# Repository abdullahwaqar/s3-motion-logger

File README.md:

# S3 Motion Logger

ESP32-S3 motion logging board. It logs 6-axis IMU data to a microSD card and streams it over USB, BLE or Wi-Fi. It runs from a single-cell LiPo and charges over USB-C.

**Schematic:** [docs/s3-motion-logger-schematic.pdf](docs/s3-motion-logger-schematic.pdf)

## Specs

|            |                                                        |
| ---------- | ------------------------------------------------------ |
| MCU        | ESP32-S3-WROOM-1-N16R8 (16 MB flash, 8 MB octal PSRAM) |
| IMU        | ICM-42688-P, 4-wire SPI, data-ready interrupt          |
| Storage    | microSD, SDMMC 4-bit                                   |
| Power in   | USB-C, 5 V                                             |
| Battery    | 1S LiPo, JST-PH, charged at 500 mA                     |
| Charger    | BQ24074 with power path (board runs while charging)    |
| 3.3 V rail | TPS63802 buck-boost, 600 mA design budget              |
| Expansion  | Qwiic (I2C) with cuttable pull-ups                     |
| Board      | 50 x 44.5 mm, 4 layers, 1.6 mm, JLCPCB-oriented rules  |

## Block diagram

## Design decisions

- **Charger boots in a safe mode.** The BQ24074 defaults to 500 mA through the EN1/EN2 pull resistors. Firmware raises the input limit only after reading the USB-C CC voltage on the ADC and confirming a 1.5 A or 3 A source.
- **Buck-boost instead of an LDO.** The TPS63802 holds 3.3 V while the battery sags below 3.3 V. Output is set by a 511k/91k divider to 3.31 V.
- **Reverse battery protection.** A P-FET in the battery line protects the charger. JST LiPo polarity is not standardized between vendors, so this is a common failure on real boards.
- **Switched battery sense.** A divider gated by a P-FET and an N-FET draws no current when idle. It reads on ADC1.
- **USB-C done properly.** Separate 5.1k Rd on CC1 and CC2, ESD protection (USBLC6-2SC6) at the connector, and D+/D- defined as a differential pair.
- **GPIO map avoids known traps.** No use of the strapping pins, the octal PSRAM pins (IO35 to IO37), or ADC2 (unusable while Wi-Fi is running). Full map on the MCU sheet.
- **Datasheet-driven parts.** Pinouts and decoupling for the TPS63802 and ICM-42688-P were taken from the TI and TDK datasheets, with custom symbols in `motion_logger.kicad_sym`.
- **Stackup.** L1 signal and parts, L2 solid GND, L3 3V3, L4 signal and GND fill. The antenna sits at the board edge with a copper keep-out on all layers.

## Layout

## Power budget (3.3 V rail)

| Load                | Typical              | Peak             |
| ------------------- | -------------------- | ---------------- |
| ESP32-S3 (Wi-Fi TX) | 30 to 80 mA with BLE | about 350 mA     |
| microSD writes      | 20 mA                | about 100 mA     |
| ICM-42688-P         | about 1 mA           | about 1 mA       |
| LEDs, pull-ups      | about 5 mA           | about 5 mA       |
| **Total**           | **60 to 110 mA**     | **about 460 mA** |

## Open items

1. **No firmware yet.**

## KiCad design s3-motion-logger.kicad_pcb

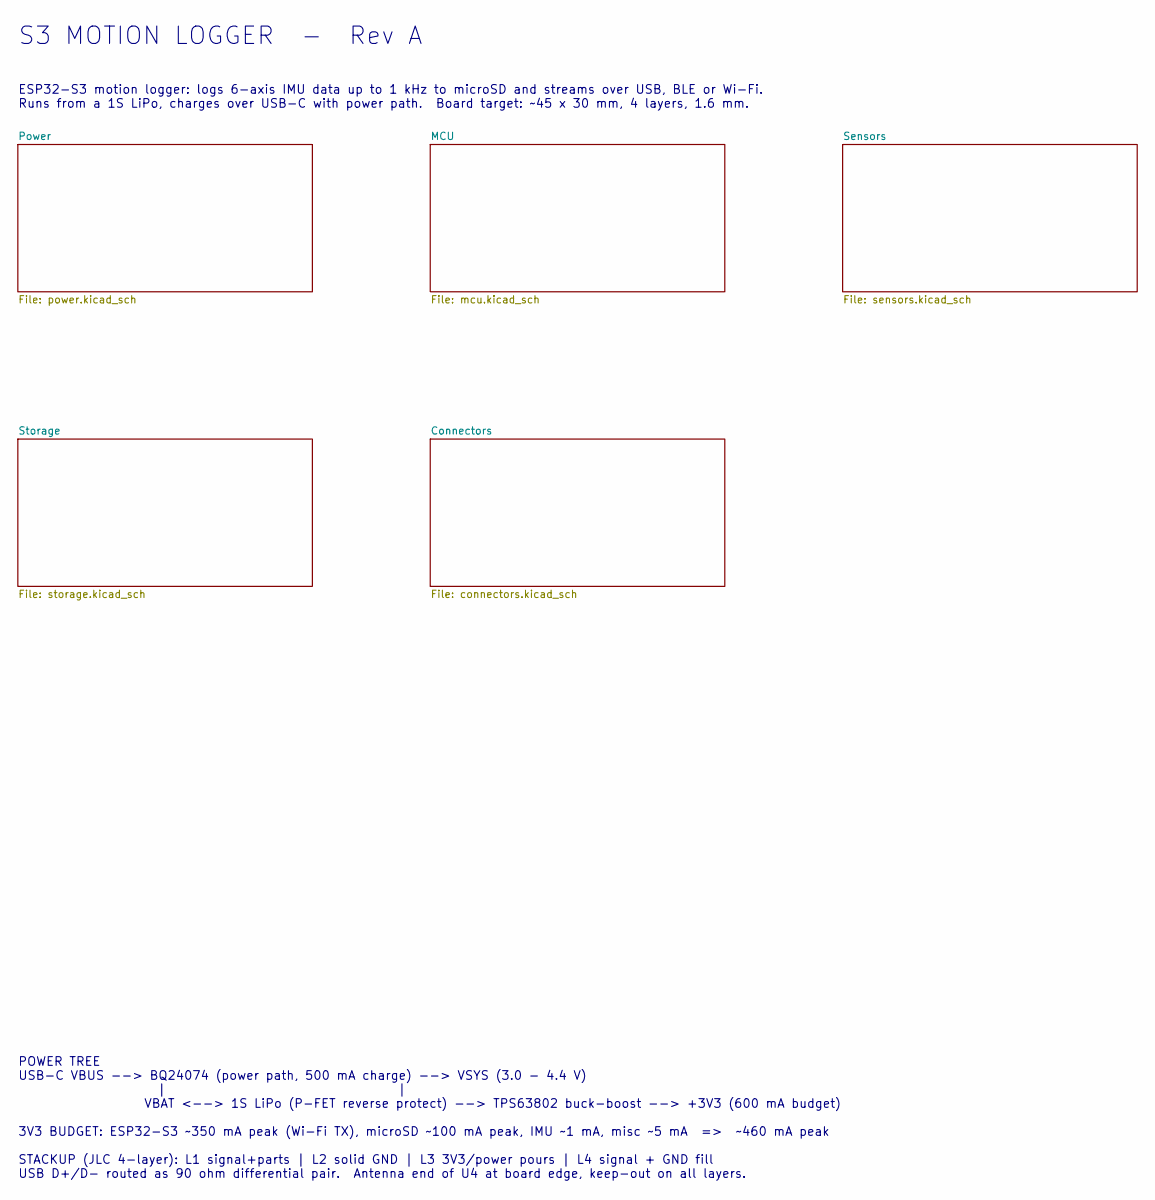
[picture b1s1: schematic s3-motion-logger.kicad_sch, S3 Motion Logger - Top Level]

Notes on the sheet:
S3 MOTION LOGGER - Rev A
ESP32-S3 motion logger: logs 6-axis IMU data up to 1 kHz to microSD and streams over USB, BLE or Wi-Fi. Runs from a 1S LiPo, charges over USB-C with power path. Board target: ~45 x 30 mm, 4 layers, 1.6 mm.
POWER TREE USB-C VBUS --> BQ24074 (power path, 500 mA charge) --> VSYS (3.0 - 4.4 V) | | VBAT <--> 1S LiPo (P-FET reverse protect) --> TPS63802 buck-boost --> +3V3 (600 mA budget) 3V3 BUDGET: ESP32-S3 ~350 mA peak (Wi-Fi TX), microSD ~100 mA peak, IMU ~1 mA, misc ~5 mA => ~460 mA peak STACKUP (JLC 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

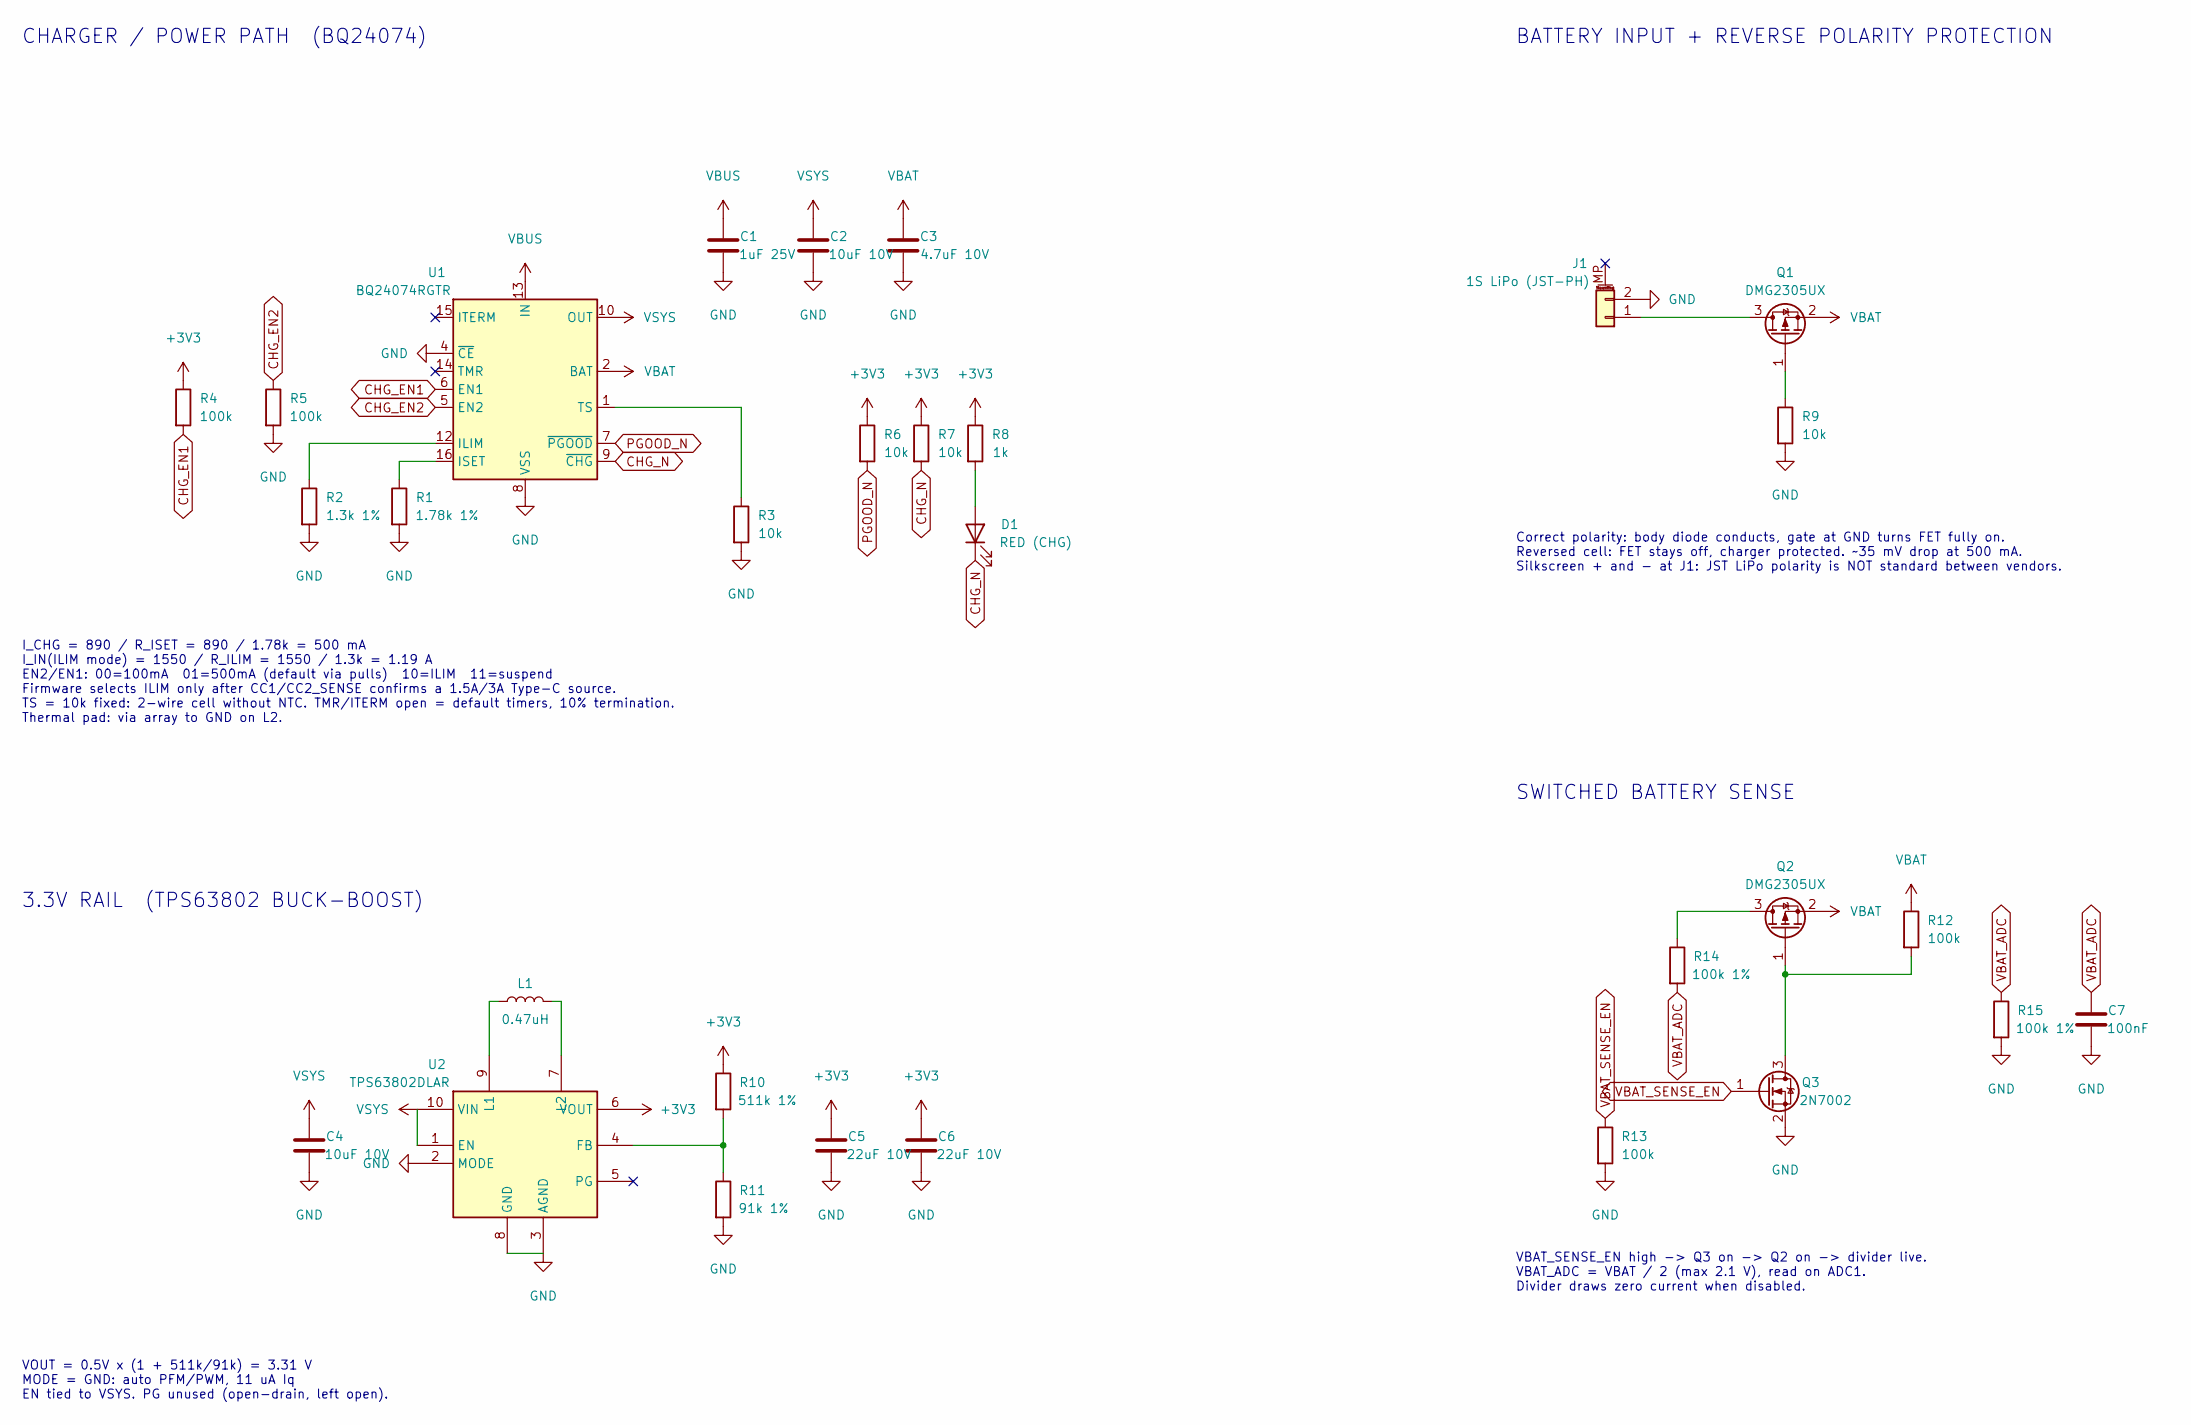
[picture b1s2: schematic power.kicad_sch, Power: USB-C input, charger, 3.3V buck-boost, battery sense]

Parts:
C1: 1uF 25V; C_0603_1608Metric
C2, C4: 10uF 10V; C_0603_1608Metric
C3: 4.7uF 10V; C_0603_1608Metric
C5, C6: 22uF 10V; C_0603_1608Metric
C7: 100nF; C_0402_1005Metric
D1: RED (CHG); LED_0603_1608Metric
J1: 1S LiPo (JST-PH); JST_PH_S2B-PH-SM4-TB_1x02-1MP_P2.00mm_Horizontal; MPN S2B-PH-SM4-TB
L1: 0.47uH; L_Murata_DFE201610P; MPN DFE201610E-R47M=P2
Q1, Q2: DMG2305UX; SOT-23; MPN DMG2305UX-7
Q3: 2N7002; SOT-23; MPN 2N7002
R1: 1.78k 1%; R_0402_1005Metric
R2: 1.3k 1%; R_0402_1005Metric
R3, R6, R7, R9: 10k; R_0402_1005Metric
R4, R5, R12, R13: 100k; R_0402_1005Metric
R8: 1k; R_0402_1005Metric
R10: 511k 1%; R_0402_1005Metric
R11: 91k 1%; R_0402_1005Metric
R14, R15: 100k 1%; R_0402_1005Metric
U1: BQ24074RGTR; VQFN-16-1EP_3x3mm_P0.5mm_EP1.6x1.6mm_ThermalVias; MPN BQ24074RGTR
U2: TPS63802DLAR; TPS63802_DLA_PLACEHOLDER; MPN TPS63802DLAR

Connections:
+3V3: C5.1, C6.1, R4.1, R6.1, R7.1, R8.1, R10.1, U2.6 (VOUT); also elsewhere on the board
BATT_IN: J1.1, Q1.3 (D)
CHGLED_A: D1.2 (A), R8.2
CHG_EN1: R4.2, U1.6 (EN1); also elsewhere on the board
CHG_EN2: R5.1, U1.5 (EN2); also elsewhere on the board
CHG_N: D1.1 (K), R7.2, U1.9 (~CHG); also elsewhere on the board
FB: R10.2, R11.1, U2.4 (FB)
GND: C1.2, C2.2, C3.2, C4.2, C5.2, C6.2, C7.2, J1.2, Q3.2 (S), R1.2, R2.2, R3.2, R5.2, R9.2, R11.2, R13.2, R15.2, U1.4 (~CE), U1.8 (VSS), U1.17 (VSS), U2.2 (MODE), U2.3 (AGND), U2.8 (GND); also elsewhere on the board
ILIM: R2.1, U1.12 (ILIM)
ISET: R1.1, U1.16 (ISET)
PGOOD_N: R6.2, U1.7 (~PGOOD); also elsewhere on the board
Q1_G: Q1.1 (G), R9.1
Q2_G: Q2.1 (G), Q3.3 (D), R12.2
SW1: L1.1, U2.9 (L1)
SW2: L1.2, U2.7 (L2)
TS: R3.1, U1.1 (TS)
VBAT: C3.1, Q1.2 (S), Q2.2 (S), R12.1, U1.2 (BAT), U1.3 (BAT); also elsewhere on the board
VBAT_ADC: C7.1, R14.2, R15.1; also elsewhere on the board
VBAT_SENSE_EN: Q3.1 (G), R13.1; also elsewhere on the board
VBUS: C1.1, U1.13 (IN); also elsewhere on the board
VDIV_TOP: Q2.3 (D), R14.1
VSYS: C2.1, C4.1, U1.10 (OUT), U1.11 (OUT), U2.1 (EN), U2.10 (VIN); also elsewhere on the board

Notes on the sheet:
CHARGER / POWER PATH (BQ24074)
I_CHG = 890 / R_ISET = 890 / 1.78k = 500 mA I_IN(ILIM mode) = 1550 / R_ILIM = 1550 / 1.3k = 1.19 A EN2/EN1: 00=100mA 01=500mA (default via pulls) 10=ILIM 11=suspend Firmware selects ILIM only after CC1/CC2_SENSE confirms a 1.5A/3A Type-C source. TS = 10k fixed: 2-wire cell without NTC. TMR/ITERM op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
BATTERY INPUT + REVERSE POLARITY PROTECTION
Correct polarity: body diode conducts, gate at GND turns FET fully on. Reversed cell: FET stays off, charger protected. ~35 mV drop at 500 mA. Silkscreen + and - at J1: JST LiPo polarity is NOT standard between vendors.
3.3V RAIL (TPS63802 BUCK-BOOST)
VOUT = 0.5V x (1 + 511k/91k) = 3.31 V MODE = GND: auto PFM/PWM, 11 uA Iq EN tied to VSYS. PG unused (open-drain, left open).
SWITCHED BATTERY SENSE
VBAT_SENSE_EN high -> Q3 on -> Q2 on -> divider live. VBAT_ADC = VBAT / 2 (max 2.1 V), read on ADC1. Divider draws zero current when disabled.

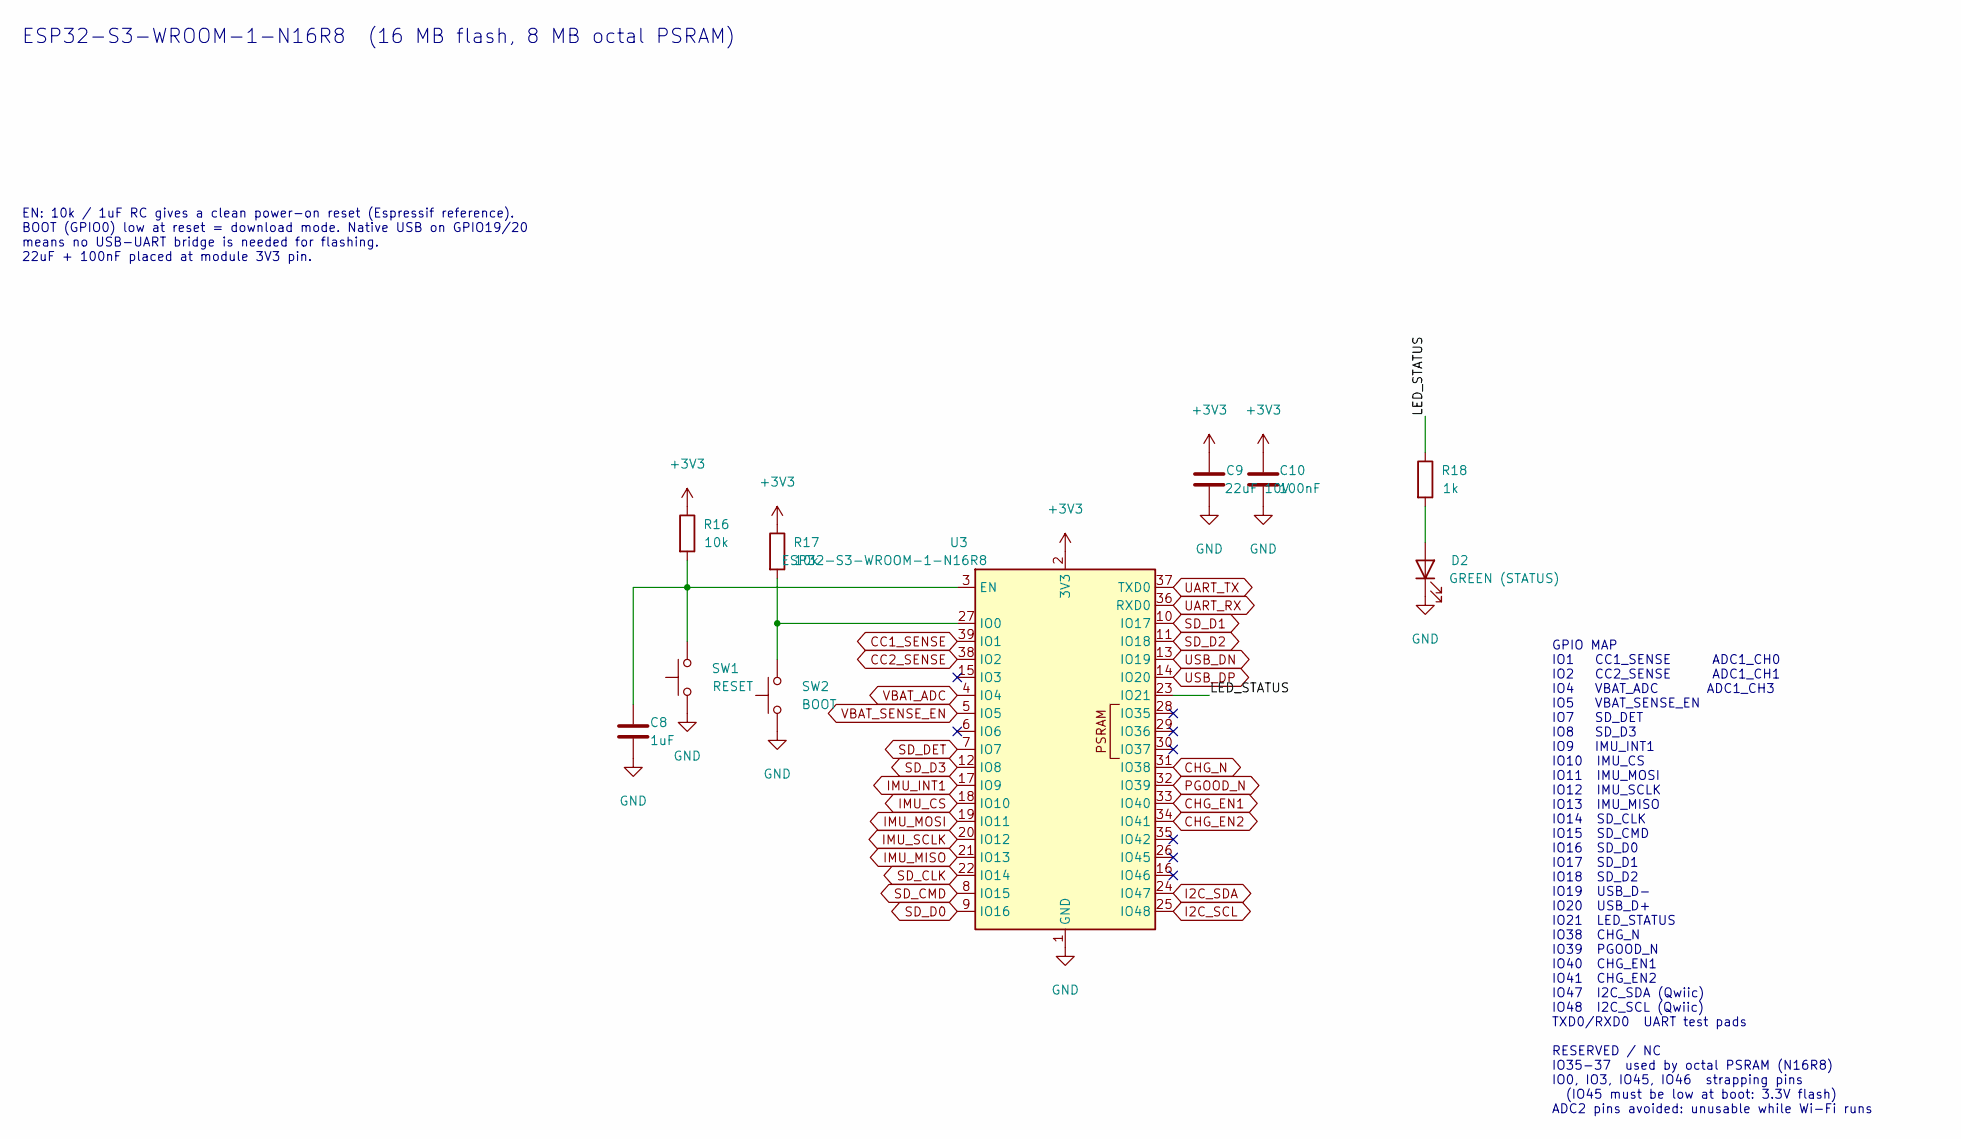
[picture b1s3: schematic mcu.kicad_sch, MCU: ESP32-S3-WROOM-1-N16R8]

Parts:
C8: 1uF; C_0402_1005Metric
C9: 22uF 10V; C_0603_1608Metric
C10: 100nF; C_0402_1005Metric
D2: GREEN (STATUS); LED_0603_1608Metric
R16, R17: 10k; R_0402_1005Metric
R18: 1k; R_0402_1005Metric
SW1: RESET; SW_SPST_PTS810; MPN PTS810 SJM 250 SMTR LFS
SW2: BOOT; SW_SPST_PTS810; MPN PTS810 SJM 250 SMTR LFS
U3: ESP32-S3-WROOM-1-N16R8; ESP32-S3-WROOM-1; MPN ESP32-S3-WROOM-1-N16R8

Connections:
+3V3: C9.1, C10.1, R16.1, R17.1, U3.2 (3V3); also elsewhere on the board
BOOT: R17.2, SW2.2, U3.27 (IO0)
CC1_SENSE: U3.39 (IO1); also elsewhere on the board
CC2_SENSE: U3.38 (IO2); also elsewhere on the board
CHG_EN1: U3.33 (IO40); also elsewhere on the board
CHG_EN2: U3.34 (IO41); also elsewhere on the board
CHG_N: U3.31 (IO38); also elsewhere on the board
EN: C8.1, R16.2, SW1.2, U3.3 (EN)
GND: C8.2, C9.2, C10.2, D2.1 (K), SW1.1, SW2.1, U3.1 (GND), U3.40 (GND), U3.41 (GND); also elsewhere on the board
I2C_SCL: U3.25 (IO48); also elsewhere on the board
I2C_SDA: U3.24 (IO47); also elsewhere on the board
IMU_CS: U3.18 (IO10); also elsewhere on the board
IMU_INT1: U3.17 (IO9); also elsewhere on the board
IMU_MISO: U3.21 (IO13); also elsewhere on the board
IMU_MOSI: U3.19 (IO11); also elsewhere on the board
IMU_SCLK: U3.20 (IO12); also elsewhere on the board
LED_STATUS: R18.1, U3.23 (IO21)
LED_ST_A: D2.2 (A), R18.2
PGOOD_N: U3.32 (IO39); also elsewhere on the board
SD_CLK: U3.22 (IO14); also elsewhere on the board
SD_CMD: U3.8 (IO15); also elsewhere on the board
SD_D0: U3.9 (IO16); also elsewhere on the board
SD_D1: U3.10 (IO17); also elsewhere on the board
SD_D2: U3.11 (IO18); also elsewhere on the board
SD_D3: U3.12 (IO8); also elsewhere on the board
SD_DET: U3.7 (IO7); also elsewhere on the board
UART_RX: U3.36 (RXD0); also elsewhere on the board
UART_TX: U3.37 (TXD0); also elsewhere on the board
USB_DN: U3.13 (IO19); also elsewhere on the board
USB_DP: U3.14 (IO20); also elsewhere on the board
VBAT_ADC: U3.4 (IO4); also elsewhere on the board
VBAT_SENSE_EN: U3.5 (IO5); also elsewhere on the board

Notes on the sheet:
ESP32-S3-WROOM-1-N16R8 (16 MB flash, 8 MB octal PSRAM)
EN: 10k / 1uF RC gives a clean power-on reset (Espressif reference). BOOT (GPIO0) low at reset = download mode. Native USB on GPIO19/20 means no USB-UART bridge is needed for flashing. 22uF + 100nF placed at module 3V3 pin.
GPIO MAP IO1 CC1_SENSE ADC1_CH0 IO2 CC2_SENSE ADC1_CH1 IO4 VBAT_ADC ADC1_CH3 IO5 VBAT_SENSE_EN IO7 SD_DET IO8 SD_D3 IO9 IMU_INT1 IO10 IMU_CS IO11 IMU_MOSI IO12 IMU_SCLK IO13 IMU_MISO IO14 SD_CLK IO15 SD_CMD IO16 SD_D0 IO17 SD_D1 IO18 SD_D2 IO19 USB_D- IO20 USB_D+ IO21 LED_STATUS IO38 CHG_N IO39 PGO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

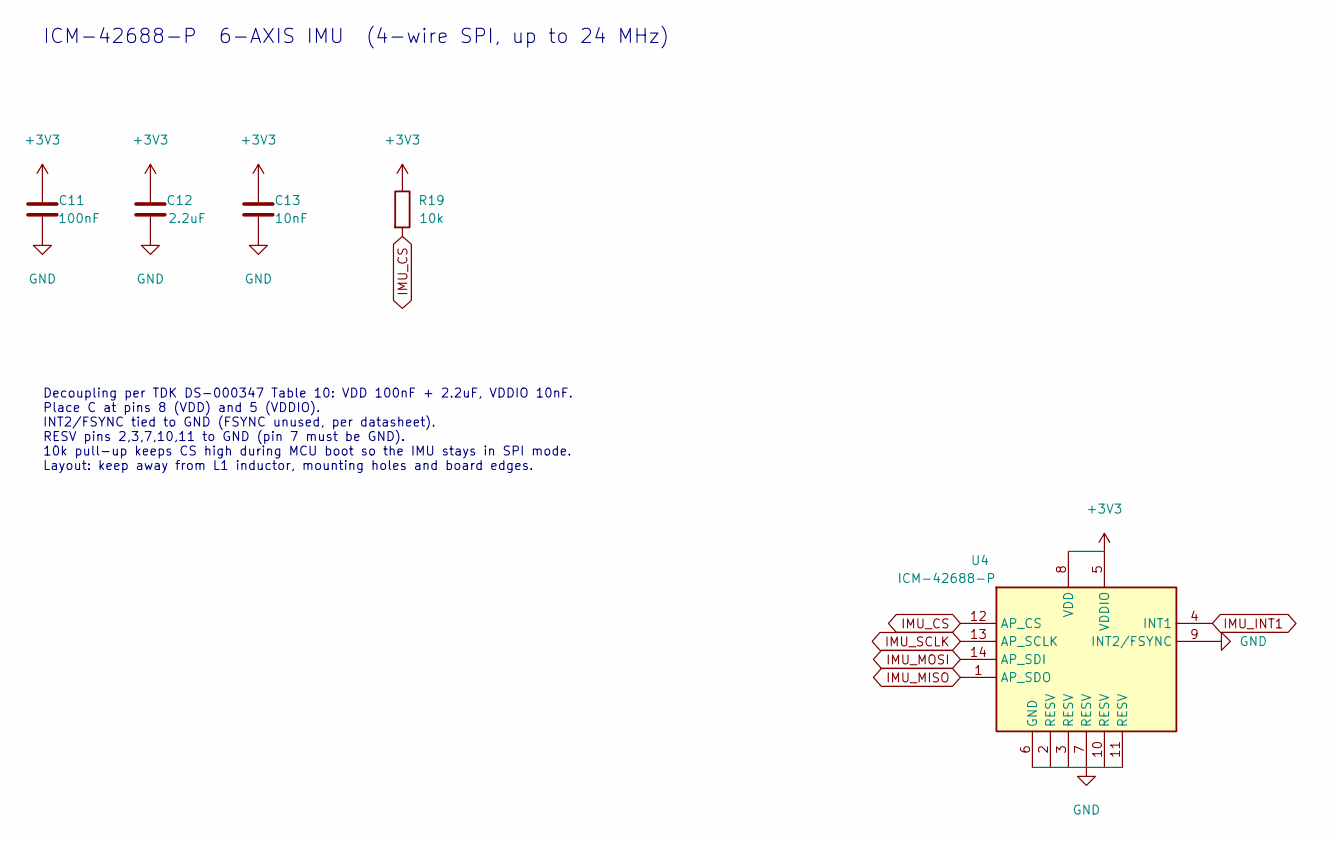
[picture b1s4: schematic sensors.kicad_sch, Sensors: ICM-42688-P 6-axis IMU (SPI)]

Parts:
C11: 100nF; C_0402_1005Metric
C12: 2.2uF; C_0402_1005Metric
C13: 10nF; C_0402_1005Metric
R19: 10k; R_0402_1005Metric
U4: ICM-42688-P; LGA-14_3x2.5mm_P0.5mm_LayoutBorder3x4y; MPN ICM-42688-P

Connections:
+3V3: C11.1, C12.1, C13.1, R19.1, U4.5 (VDDIO), U4.8 (VDD); also elsewhere on the board
GND: C11.2, C12.2, C13.2, U4.2 (RESV), U4.3 (RESV), U4.6 (GND), U4.7 (RESV), U4.9 (INT2/FSYNC), U4.10 (RESV), U4.11 (RESV); also elsewhere on the board
IMU_CS: R19.2, U4.12 (AP_CS); also elsewhere on the board
IMU_INT1: U4.4 (INT1); also elsewhere on the board
IMU_MISO: U4.1 (AP_SDO); also elsewhere on the board
IMU_MOSI: U4.14 (AP_SDI); also elsewhere on the board
IMU_SCLK: U4.13 (AP_SCLK); also elsewhere on the board

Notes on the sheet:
ICM-42688-P 6-AXIS IMU (4-wire SPI, up to 24 MHz)
Decoupling per TDK DS-000347 Table 10: VDD 100nF + 2.2uF, VDDIO 10nF. Place C at pins 8 (VDD) and 5 (VDDIO). INT2/FSYNC tied to GND (FSYNC unused, per datasheet). RESV pins 2,3,7,10,11 to GND (pin 7 must be GND). 10k pull-up keeps CS high during MCU boot so the IMU stays in SPI mode. Layout: keep a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

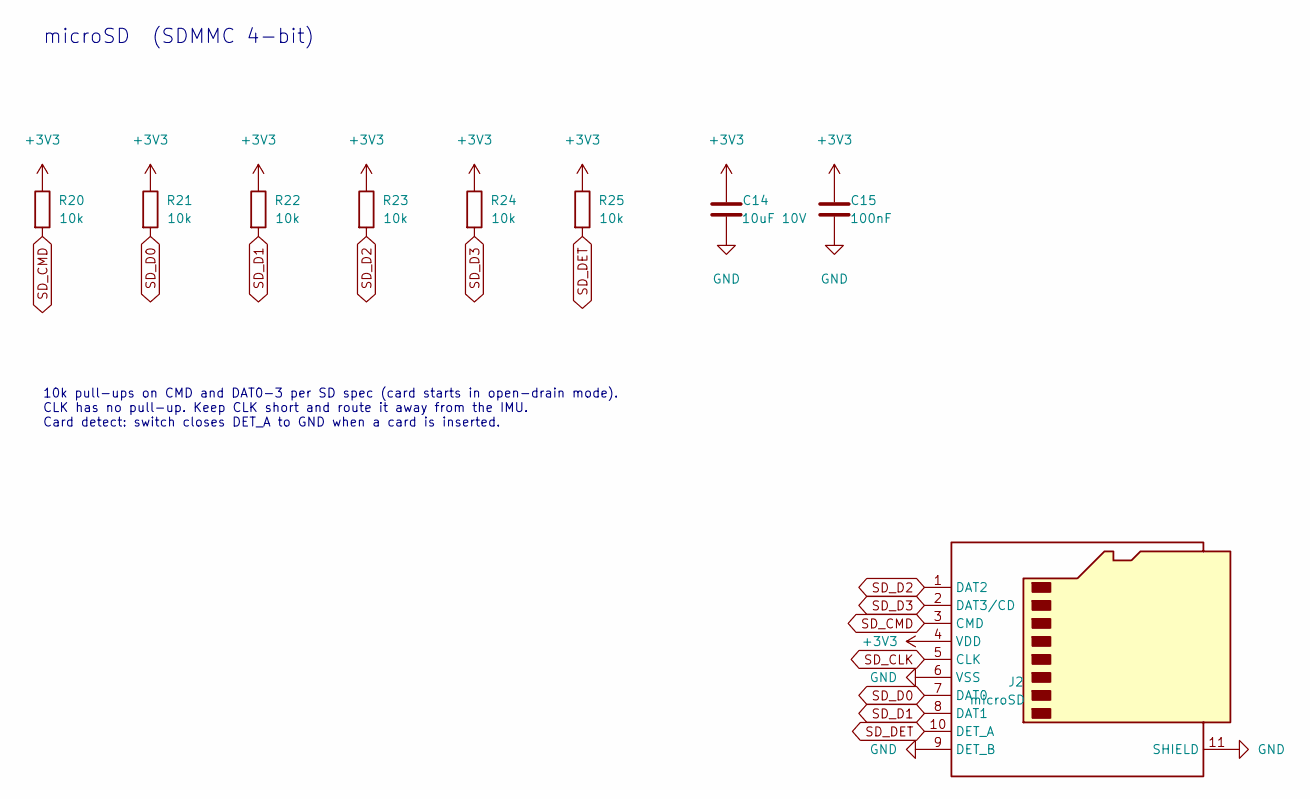
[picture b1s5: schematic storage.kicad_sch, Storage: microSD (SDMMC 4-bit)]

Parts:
C14: 10uF 10V; C_0603_1608Metric
C15: 100nF; C_0402_1005Metric
J2: microSD; microSD_HC_Hirose_DM3AT-SF-PEJM5; MPN DM3AT-SF-PEJM5
R20, R21, R22, R23, R24, R25: 10k; R_0402_1005Metric

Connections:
+3V3: C14.1, C15.1, J2.4 (VDD), R20.1, R21.1, R22.1, R23.1, R24.1, R25.1; also elsewhere on the board
GND: C14.2, C15.2, J2.6 (VSS), J2.9 (DET_B), J2.11 (SHIELD); also elsewhere on the board
SD_CLK: J2.5 (CLK); also elsewhere on the board
SD_CMD: J2.3 (CMD), R20.2; also elsewhere on the board
SD_D0: J2.7 (DAT0), R21.2; also elsewhere on the board
SD_D1: J2.8 (DAT1), R22.2; also elsewhere on the board
SD_D2: J2.1 (DAT2), R23.2; also elsewhere on the board
SD_D3: J2.2 (DAT3/CD), R24.2; also elsewhere on the board
SD_DET: J2.10 (DET_A), R25.2; also elsewhere on the board

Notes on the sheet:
microSD (SDMMC 4-bit)
10k pull-ups on CMD and DAT0-3 per SD spec (card starts in open-drain mode). CLK has no pull-up. Keep CLK short and route it away from the IMU. Card detect: switch closes DET_A to GND when a card is inserted.

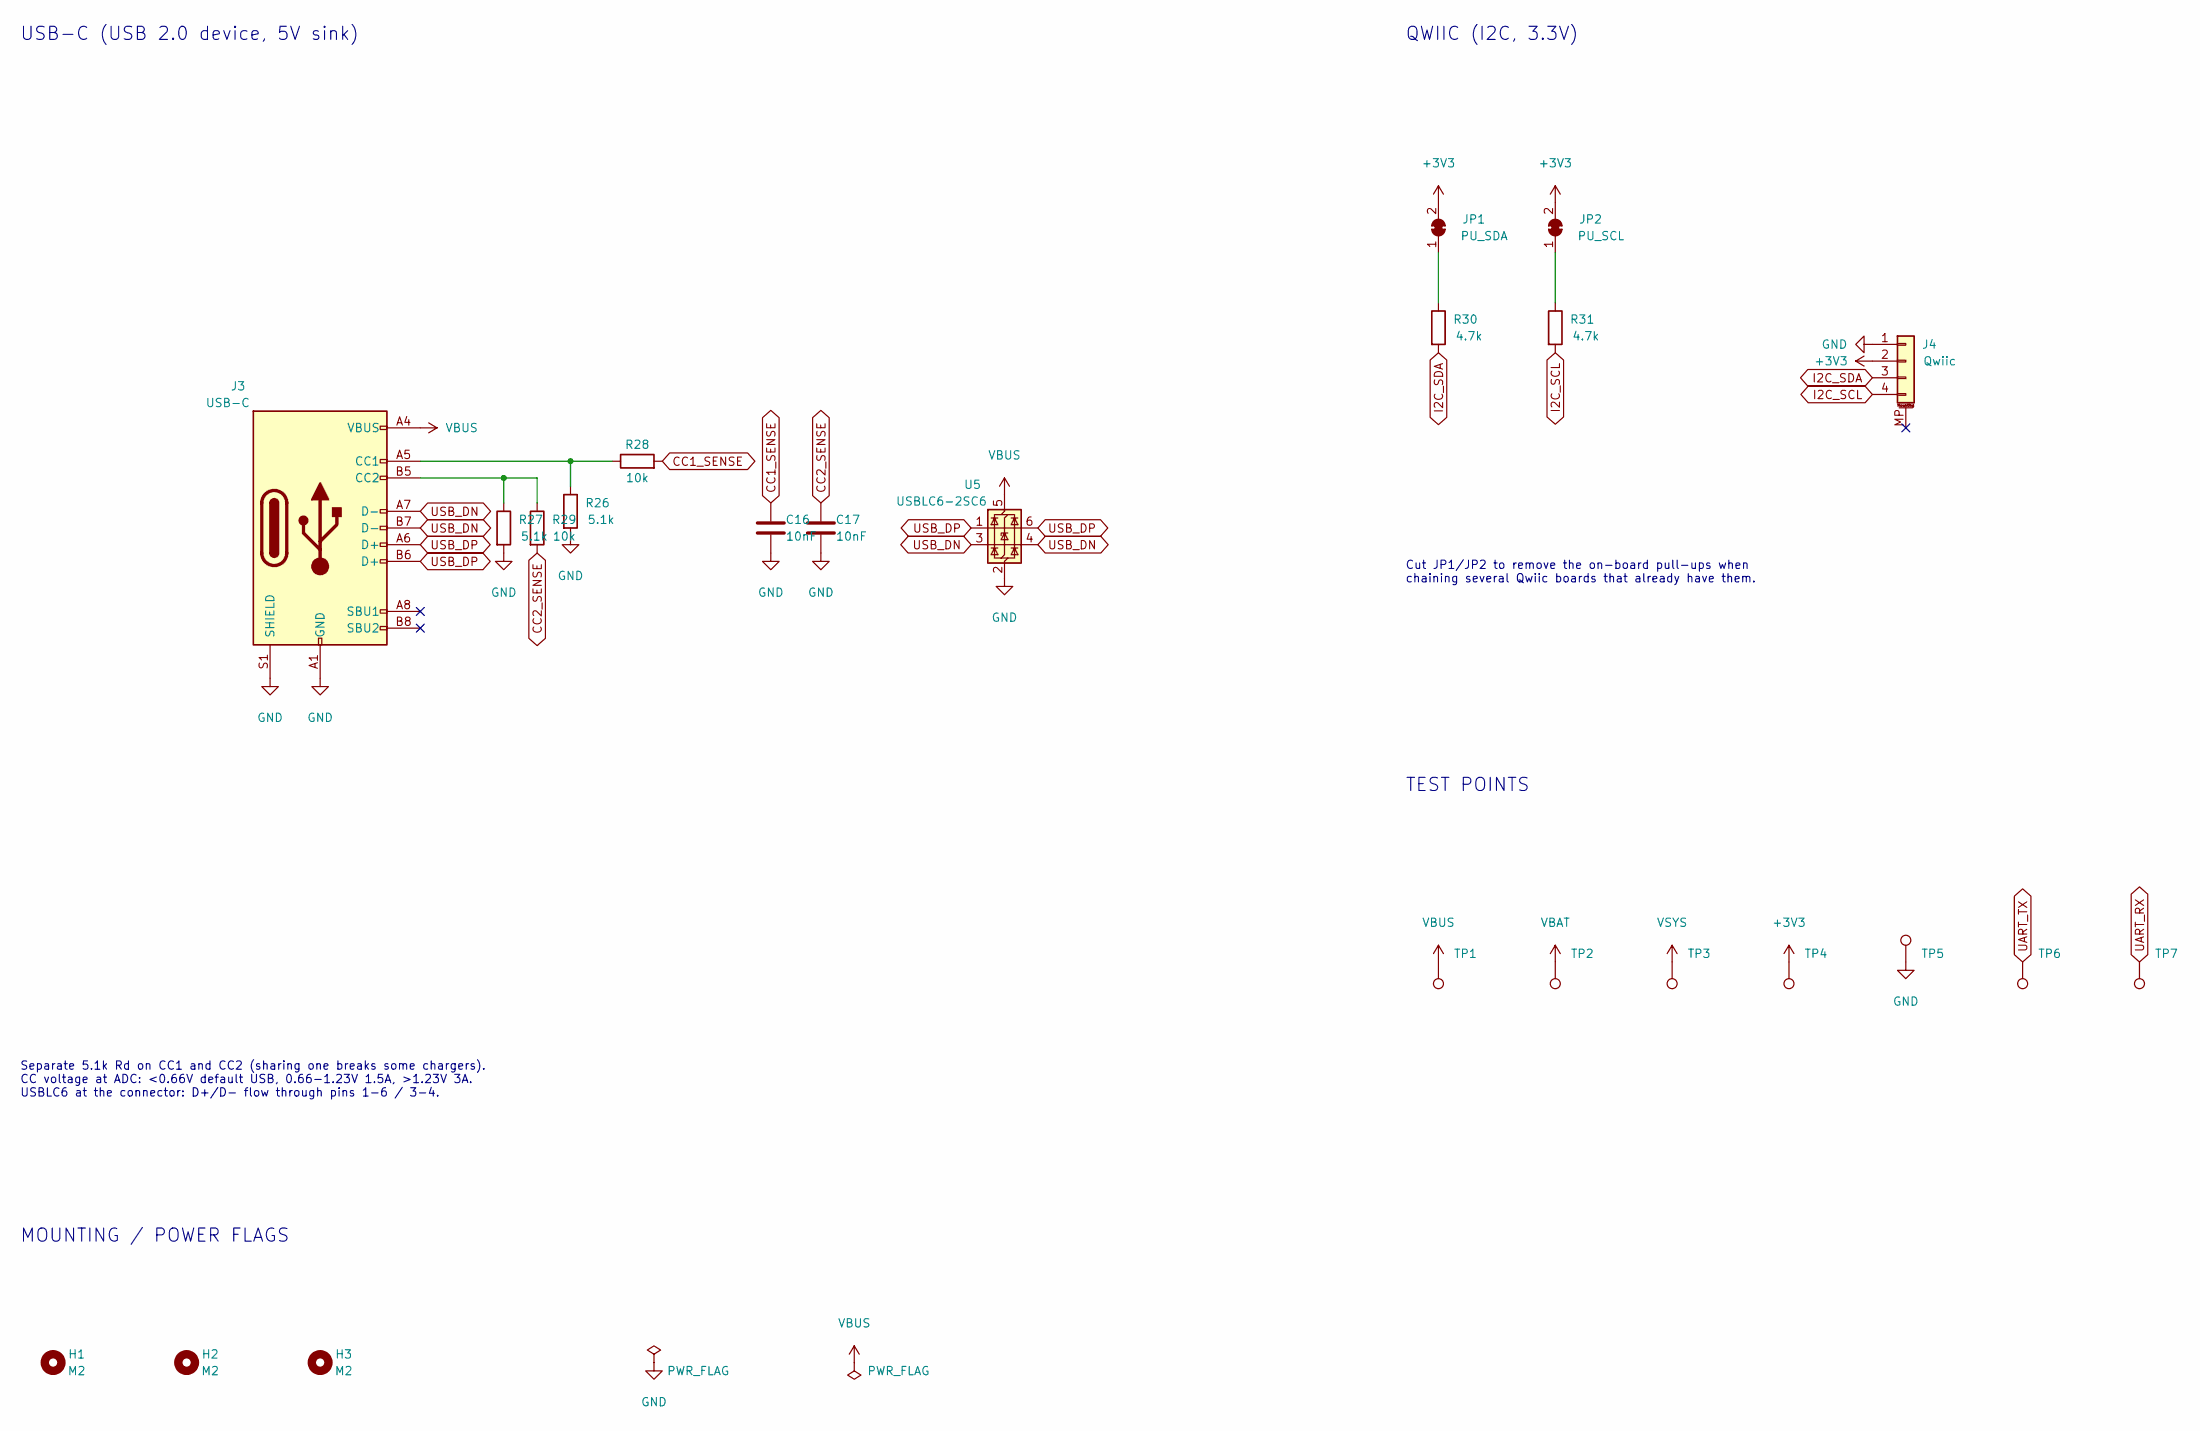
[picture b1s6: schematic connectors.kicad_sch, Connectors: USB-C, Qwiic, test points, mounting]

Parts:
C16, C17: 10nF; C_0402_1005Metric
H1, H2, H3: M2; MountingHole_2.2mm_M2
J3: USB-C; USB_C_Receptacle_HRO_TYPE-C-31-M-12; MPN TYPE-C-31-M-12
J4: Qwiic; JST_SH_SM04B-SRSS-TB_1x04-1MP_P1.00mm_Horizontal; MPN SM04B-SRSS-TB
JP1: PU_SDA; SolderJumper-2_P1.3mm_Bridged_RoundedPad1.0x1.5mm
JP2: PU_SCL; SolderJumper-2_P1.3mm_Bridged_RoundedPad1.0x1.5mm
R26, R27: 5.1k; R_0402_1005Metric
R28, R29: 10k; R_0402_1005Metric
R30, R31: 4.7k; R_0402_1005Metric
TP1: VBUS; TestPoint_Pad_D1.0mm
TP2: VBAT; TestPoint_Pad_D1.0mm
TP3: VSYS; TestPoint_Pad_D1.0mm
TP4: +3V3; TestPoint_Pad_D1.0mm
TP5: GND; TestPoint_Pad_D1.0mm
TP6: UART_TX; TestPoint_Pad_D1.0mm
TP7: UART_RX; TestPoint_Pad_D1.0mm
U5: USBLC6-2SC6; SOT-23-6; MPN USBLC6-2SC6

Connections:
+3V3: J4.2, JP1.2 (B), JP2.2 (B), TP4.1; also elsewhere on the board
CC1: J3.A5 (CC1), R26.1, R28.1
CC1_SENSE: C16.1, R28.2; also elsewhere on the board
CC2: J3.B5 (CC2), R27.1, R29.1
CC2_SENSE: C17.1, R29.2; also elsewhere on the board
GND: C16.2, C17.2, J3.A1 (GND), J3.A12 (GND), J3.B1 (GND), J3.B12 (GND), J3.S1 (SHIELD), J4.1, R26.2, R27.2, TP5.1, U5.2 (GND); also elsewhere on the board
I2C_PU_SCL: JP2.1 (A), R31.1
I2C_PU_SDA: JP1.1 (A), R30.1
I2C_SCL: J4.4, R31.2; also elsewhere on the board
I2C_SDA: J4.3, R30.2; also elsewhere on the board
UART_RX: TP7.1; also elsewhere on the board
UART_TX: TP6.1; also elsewhere on the board
USB_DN: J3.A7 (D-), J3.B7 (D-), U5.3 (I/O2), U5.4 (I/O2); also elsewhere on the board
USB_DP: J3.A6 (D+), J3.B6 (D+), U5.1 (I/O1), U5.6 (I/O1); also elsewhere on the board
VBAT: TP2.1; also elsewhere on the board
VBUS: J3.A4 (VBUS), J3.A9 (VBUS), J3.B4 (VBUS), J3.B9 (VBUS), TP1.1, U5.5 (VBUS); also elsewhere on the board
VSYS: TP3.1; also elsewhere on the board

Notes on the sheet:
USB-C (USB 2.0 device, 5V sink)
Separate 5.1k Rd on CC1 and CC2 (sharing one breaks some chargers). CC voltage at ADC: <0.66V default USB, 0.66-1.23V 1.5A, >1.23V 3A. USBLC6 at the connector: D+/D- flow through pins 1-6 / 3-4.
QWIIC (I2C, 3.3V)
Cut JP1/JP2 to remove the on-board pull-ups when chaining several Qwiic boards that already have them.
TEST POINTS
MOUNTING / POWER FLAGS

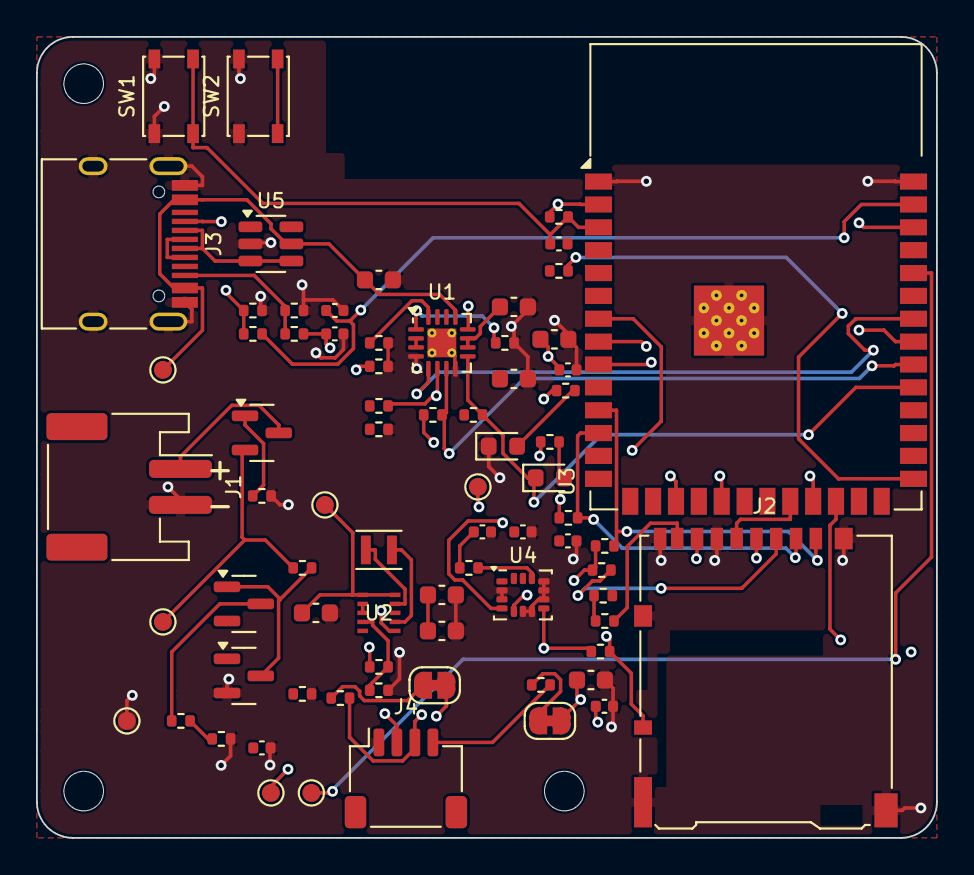
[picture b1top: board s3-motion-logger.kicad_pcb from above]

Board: 4 copper layers, 50.0 x 44.5 mm, 77 parts (0 on the bottom side), 50 nets.
